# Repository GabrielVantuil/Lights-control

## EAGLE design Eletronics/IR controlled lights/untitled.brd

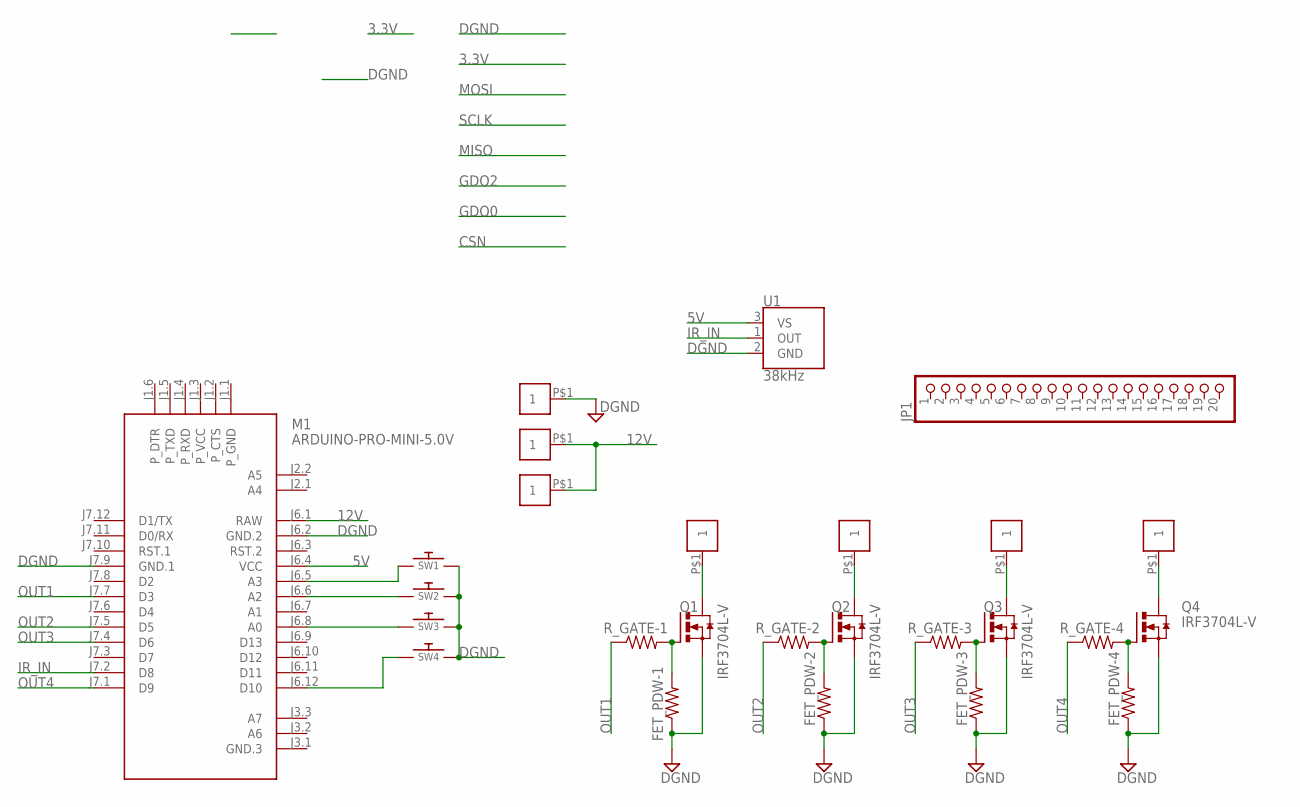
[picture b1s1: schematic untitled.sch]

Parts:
FET_PDW-1, FET_PDW-2, FET_PDW-3, FET_PDW-4: RESISTOR0603-RES; 0603-RES
JP1: PINHD-1X20; 1X20
M1: ARDUINO-PRO-MINI-5.0V; ARDUINO-PRO-MINI
Q1, Q2, Q3, Q4: IRF3704L-V; TO262-V
R_GATE-1, R_GATE-2, R_GATE-3, R_GATE-4: RESISTOR0603-RES; 0603-RES
SW1, SW2, SW3, SW4: SWITCH_PUSHBUTTONC&K_KSS; BTN_CK_KSS
U1: 38kHz; TSOP382
U$2, U$3, U$4, U$5, U$6, U$7, U$8: 1X01_2.54MM

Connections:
5V: M1.J6.4 (VCC), U1.3 (VS)
12V: M1.J6.1 (RAW), U$5.P$1, U$8.P$1
DGND: FET_PDW-1.1, FET_PDW-2.1, FET_PDW-3.1, FET_PDW-4.1, M1.J6.2 (GND.2), M1.J7.9 (GND.1), Q1.3 (S), Q2.3 (S), Q3.3 (S), Q4.3 (S), SW1.P$2, SW2.P$2, SW3.P$2, SW4.P$2, U1.2 (GND), U$7.P$1
IR_IN: M1.J7.2 (D8), U1.1 (OUT)
unnamed: FET_PDW-1.2, Q1.1 (G), R_GATE-1.2
unnamed: FET_PDW-2.2, Q2.1 (G), R_GATE-2.2
unnamed: FET_PDW-3.2, Q3.1 (G), R_GATE-3.2
unnamed: Q1.2 (D), U$2.P$1
unnamed: Q2.2 (D), U$3.P$1
unnamed: Q3.2 (D), U$4.P$1
unnamed: FET_PDW-4.2, Q4.1 (G), R_GATE-4.2
unnamed: Q4.2 (D), U$6.P$1
unnamed: M1.J6.5 (A3), SW1.P$1
unnamed: M1.J6.6 (A2), SW2.P$1
unnamed: M1.J6.8 (A0), SW3.P$1
unnamed: M1.J6.12 (D10), SW4.P$1
OUT1: M1.J7.7 (D3), R_GATE-1.1
OUT2: M1.J7.5 (D5), R_GATE-2.1
OUT3: M1.J7.4 (D6), R_GATE-3.1
OUT4: M1.J7.1 (D9), R_GATE-4.1

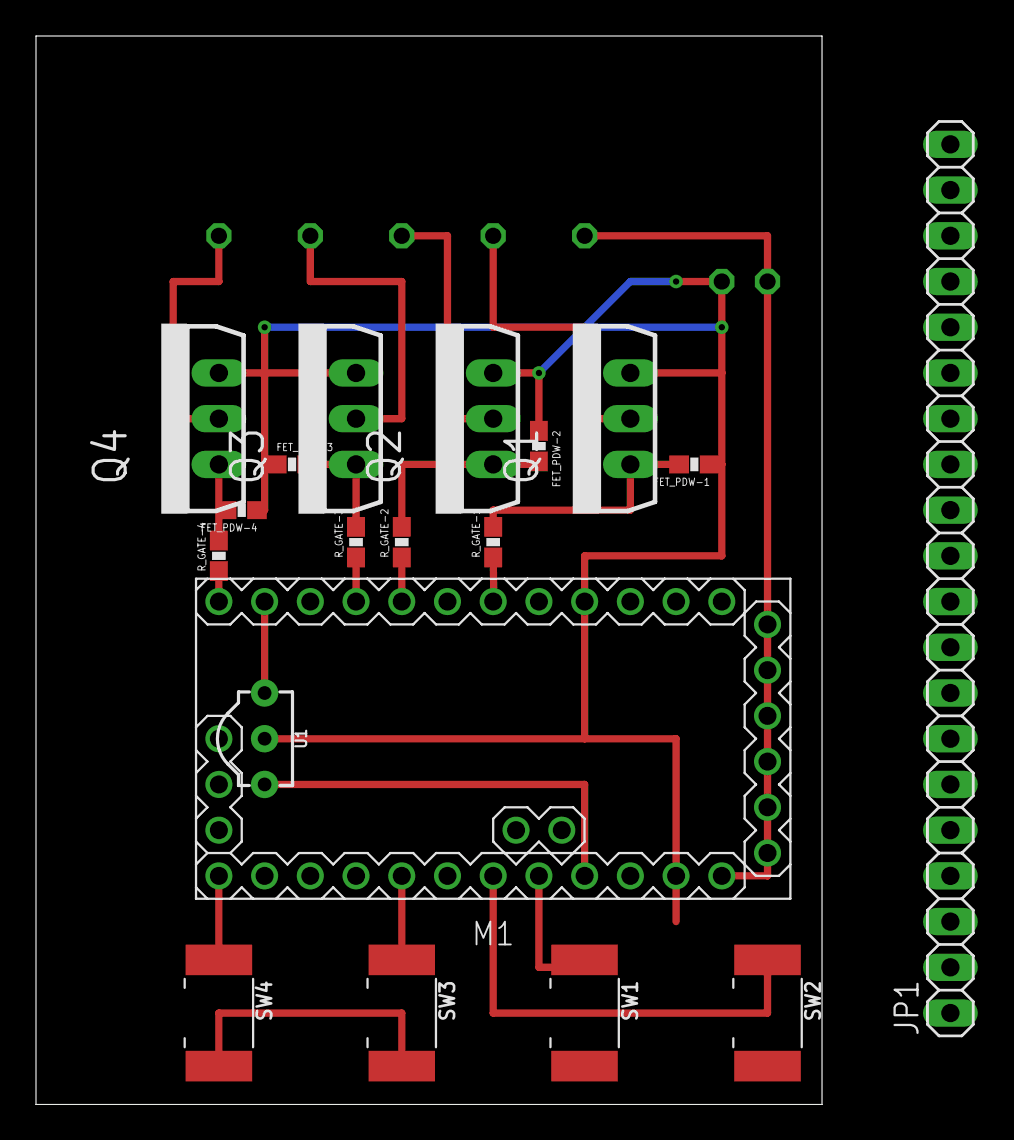
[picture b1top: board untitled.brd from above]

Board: 2 copper layers, 43.7 x 59.4 mm, 26 parts (0 on the bottom side), 20 nets.

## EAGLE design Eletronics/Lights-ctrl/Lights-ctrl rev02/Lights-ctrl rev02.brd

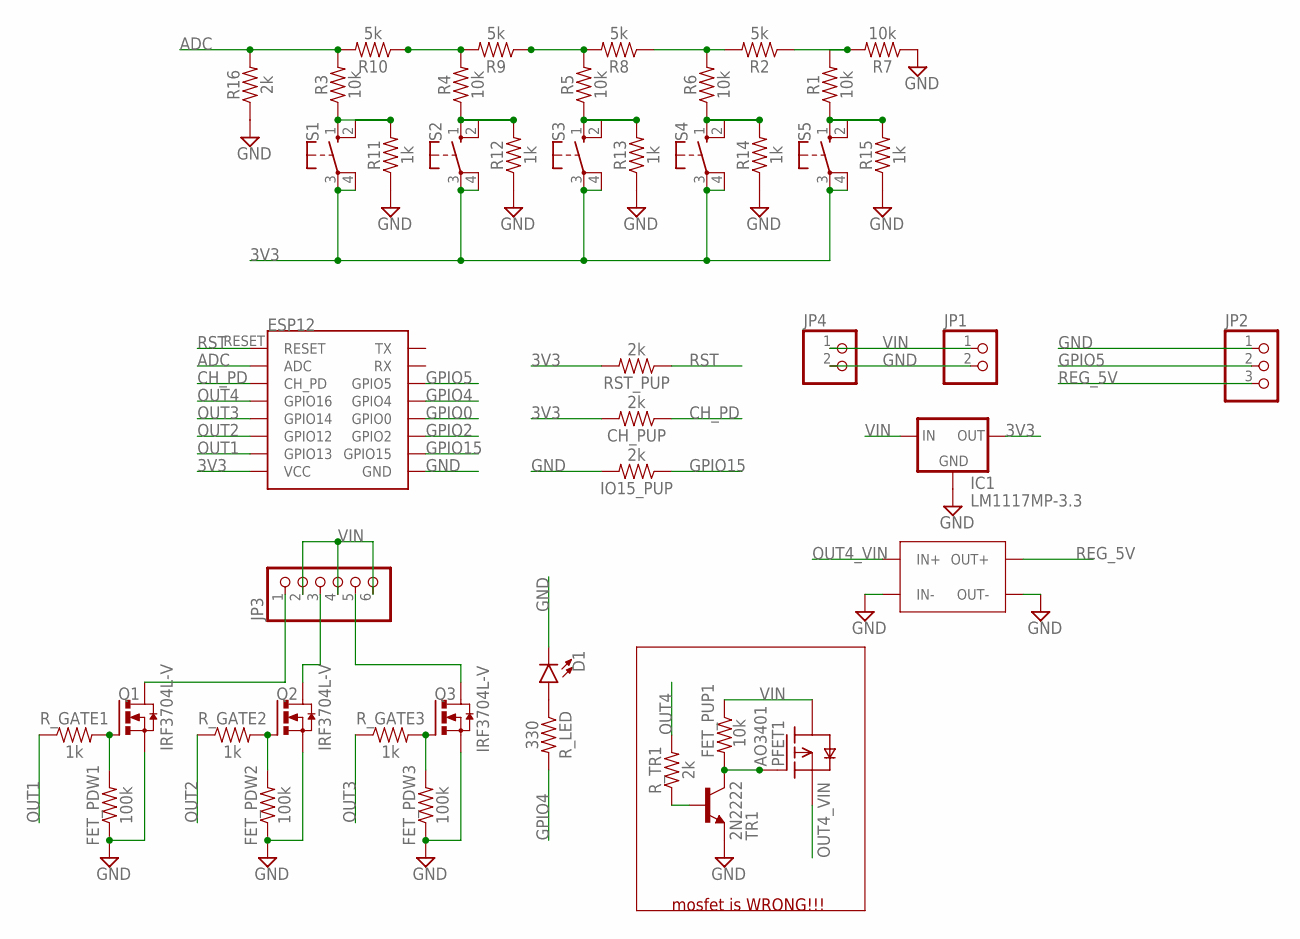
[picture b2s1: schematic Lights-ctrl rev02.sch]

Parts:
CH_PUP: 2k; 0603
D1: LED5MM-KIT; LED_5MM-KIT
FET_PDW1, FET_PDW2, FET_PDW3: 100k; 0603
FET_PUP1: 10k; 0603
IC1: LM1117MP-3.3; SOT223
IO15_PUP: 2k; 0603
JP1, JP4: PINHD-1X2; 1X02
JP2: PINHD-1X3; 1X03
JP3: PINHD-1X6/90; 1X06/90
PFET1: AO3401; SOT23-3
Q1, Q2, Q3: IRF3704L-V; TO262-V
R1, R3, R4, R5, R6, R7: 10k; 0603
R2, R8, R9, R10: 5k; 0603
R11, R12, R13, R14, R15: 1k; 0603
R16: 2k; 0603
RST_PUP: 2k; 0603
R_GATE1, R_GATE2, R_GATE3: 1k; 0603
R_LED: 330; 0603
R_TR1: 2k; 0603
S1, S2, S3, S4, S5: 10-XX; B3F-10XX
TR1: 2N2222; SOT23-BEC
U$1: ESP12E-CASTELLATED
U$4: XL4005

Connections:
3V3: CH_PUP.2, IC1.2 (OUT), IC1.4 (OUT), RST_PUP.2, S1.3, S1.4 (P1), S2.3, S2.4 (P1), S3.3, S3.4 (P1), S4.3, S4.4 (P1), S5.3, S5.4 (P1), U$1.VCC
ADC: R3.2, R10.2, R16.2, U$1.ADC
CH_PD: CH_PUP.1, U$1.CH_PD
GND: D1.K (C), FET_PDW1.1, FET_PDW2.1, FET_PDW3.1, IC1.1 (GND), IO15_PUP.2, JP1.2, JP2.1, JP4.2, Q1.3 (S), Q2.3 (S), Q3.3 (S), R7.1, R11.1, R12.1, R13.1, R14.1, R15.1, R16.1, TR1.E, U$1.GND, U$4.IN-, U$4.OUT-
GPIO0: U$1.GPIO0
GPIO2: U$1.GPIO2
GPIO4: R_LED.2, U$1.GPIO4
GPIO5: JP2.2, U$1.GPIO5
GPIO15: IO15_PUP.1, U$1.GPIO15
unnamed: JP3.1, Q1.2 (D)
unnamed: R2.2, R6.2, R8.1
unnamed: R5.2, R8.2, R9.1
unnamed: R4.2, R9.2, R10.1
unnamed: D1.A, R_LED.1
unnamed: R3.1, R11.2, S1.1 (S), S1.2 (S1)
unnamed: R_TR1.1, TR1.B
unnamed: FET_PUP1.2, PFET1.1 (G), TR1.C
unnamed: R1.1, R15.2, S5.1 (S), S5.2 (S1)
unnamed: JP3.3, Q2.2 (D)
unnamed: JP3.5, Q3.2 (D)
unnamed: FET_PDW1.2, Q1.1 (G), R_GATE1.2
unnamed: R1.2, R2.1, R7.2
unnamed: R4.1, R12.2, S2.1 (S), S2.2 (S1)
unnamed: FET_PDW2.2, Q2.1 (G), R_GATE2.2
unnamed: FET_PDW3.2, Q3.1 (G), R_GATE3.2
unnamed: R5.1, R13.2, S3.1 (S), S3.2 (S1)
unnamed: R6.1, R14.2, S4.1 (S), S4.2 (S1)
OUT1: R_GATE1.1, U$1.GPIO13
OUT2: R_GATE2.1, U$1.GPIO12
OUT3: R_GATE3.1, U$1.GPIO14
OUT4: R_TR1.2, U$1.GPIO16
OUT4_VIN: PFET1.2 (S), U$4.IN+
REG_5V: JP2.3, U$4.OUT+
RST: RST_PUP.1, U$1.RESET
VIN: FET_PUP1.1, IC1.3 (IN), JP1.1, JP3.2, JP3.4, JP3.6, JP4.1, PFET1.3 (D)

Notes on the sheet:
mosfet is WRONG!!!

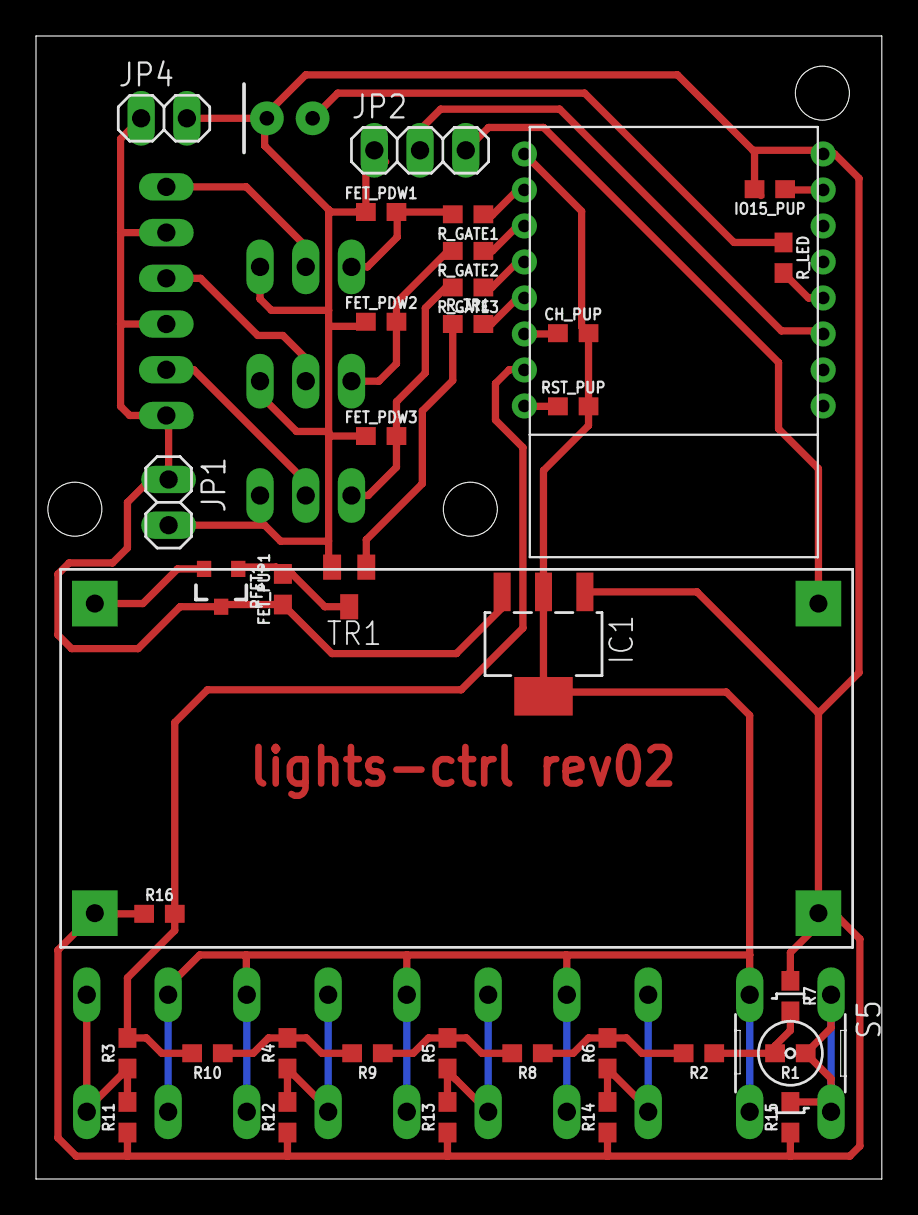
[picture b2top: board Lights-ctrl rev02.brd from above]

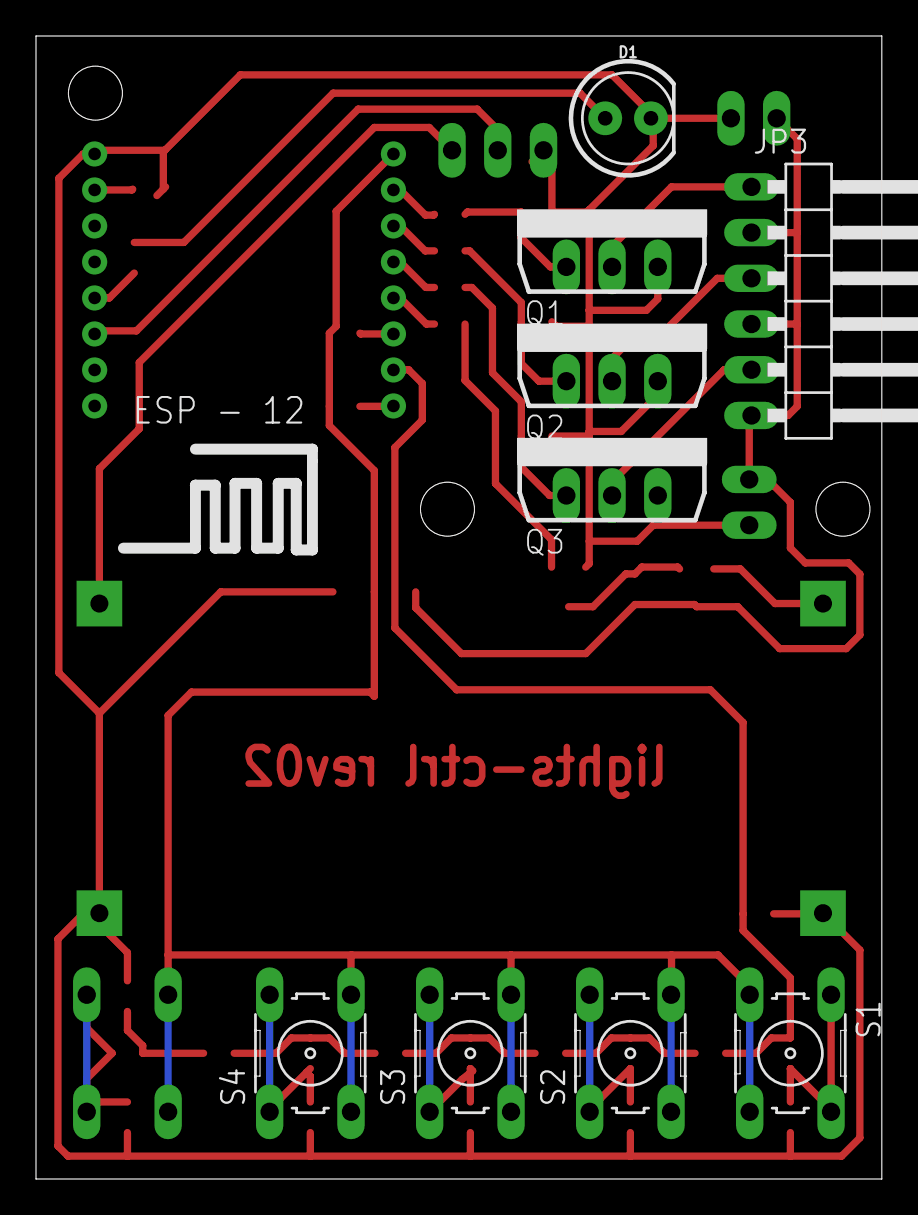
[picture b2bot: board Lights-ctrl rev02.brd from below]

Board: 2 copper layers, 47.0 x 63.5 mm, 46 parts (10 on the bottom side), 33 nets.

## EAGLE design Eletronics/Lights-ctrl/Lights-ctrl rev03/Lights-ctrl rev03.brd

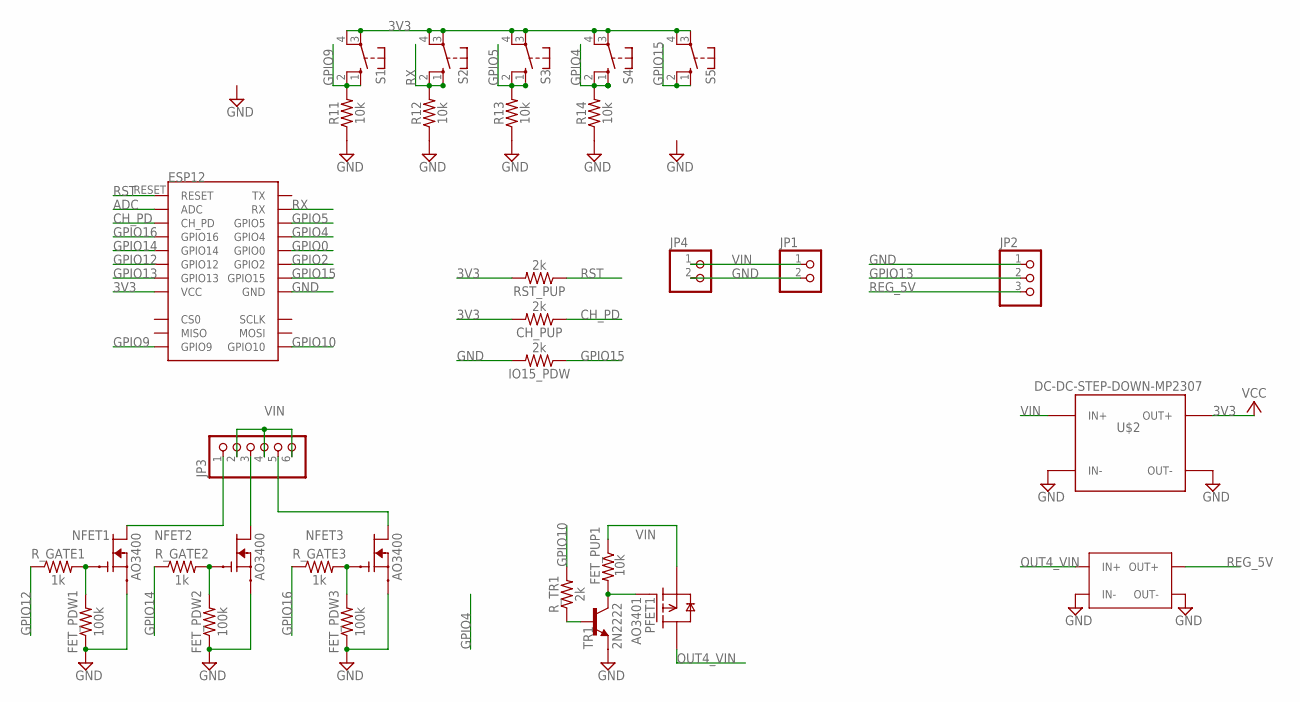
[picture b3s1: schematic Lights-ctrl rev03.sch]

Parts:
CH_PUP: 2k; 0603
FET_PDW1, FET_PDW2, FET_PDW3: 100k; 0603
FET_PUP1: 10k; 0603
IO15_PDW: 2k; 0603
JP1, JP4: PINHD-1X2; 1X02
JP2: PINHD-1X3; 1X03
JP3: PINHD-1X6/90; 1X06/90
NFET1, NFET2, NFET3: AO3400; SOT23-3
PFET1: AO3401; SOT23-3
R11, R12, R13, R14: 10k; 0603
RST_PUP: 2k; 0603
R_GATE1, R_GATE2, R_GATE3: 1k; 0603
R_TR1: 2k; 0603
S1, S2, S3, S4, S5: 10-XX; B3F-10XX
TR1: 2N2222; SOT23-BEC
U$1: ESP12E-CASTELLATED
U$2: DC-DC-STEP-DOWN-MP2307
U$4: XL4005

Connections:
3V3: CH_PUP.2, RST_PUP.2, S1.3, S1.4 (P1), S2.3, S2.4 (P1), S3.3, S3.4 (P1), S4.3, S4.4 (P1), S5.3, S5.4 (P1), U$1.VCC, U$2.OUT+
ADC: U$1.ADC
CH_PD: CH_PUP.1, U$1.CH_PD
GND: FET_PDW1.1, FET_PDW2.1, FET_PDW3.1, IO15_PDW.2, JP1.2, JP2.1, JP4.2, NFET1.2 (S), NFET2.2 (S), NFET3.2 (S), R11.1, R12.1, R13.1, R14.1, TR1.E, U$1.GND, U$2.IN-, U$2.OUT-, U$4.IN-, U$4.OUT-
GPIO0: U$1.GPIO0
GPIO2: U$1.GPIO2
GPIO4: R14.2, S4.1 (S), S4.2 (S1), U$1.GPIO4
GPIO5: R13.2, S3.1 (S), S3.2 (S1), U$1.GPIO5
GPIO9: R11.2, S1.1 (S), S1.2 (S1), U$1.GPIO9
GPIO10: R_TR1.2, U$1.GPIO10
GPIO12: R_GATE1.1, U$1.GPIO12
GPIO13: JP2.2, U$1.GPIO13
GPIO14: R_GATE2.1, U$1.GPIO14
GPIO15: IO15_PDW.1, S5.1 (S), S5.2 (S1), U$1.GPIO15
GPIO16: R_GATE3.1, U$1.GPIO16
unnamed: JP3.1, NFET1.3 (D)
unnamed: R_TR1.1, TR1.B
unnamed: FET_PUP1.2, PFET1.1 (G), TR1.C
unnamed: JP3.3, NFET2.3 (D)
unnamed: JP3.5, NFET3.3 (D)
unnamed: FET_PDW1.2, NFET1.1 (G), R_GATE1.2
unnamed: FET_PDW2.2, NFET2.1 (G), R_GATE2.2
unnamed: FET_PDW3.2, NFET3.1 (G), R_GATE3.2
OUT4_VIN: PFET1.3 (D), U$4.IN+
REG_5V: JP2.3, U$4.OUT+
RST: RST_PUP.1, U$1.RESET
RX: R12.2, S2.1 (S), S2.2 (S1), U$1.RX
VIN: FET_PUP1.1, JP1.1, JP3.2, JP3.4, JP3.6, JP4.1, PFET1.2 (S), U$2.IN+

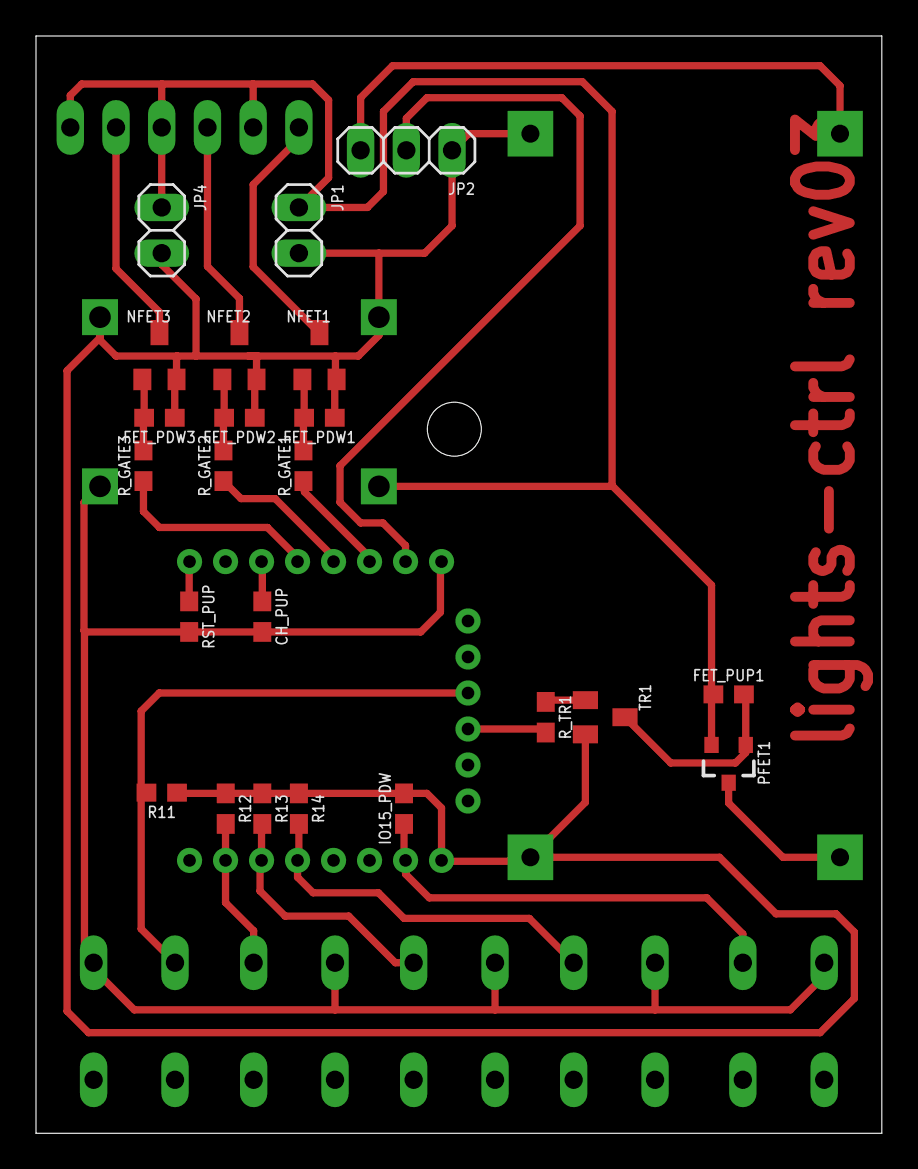
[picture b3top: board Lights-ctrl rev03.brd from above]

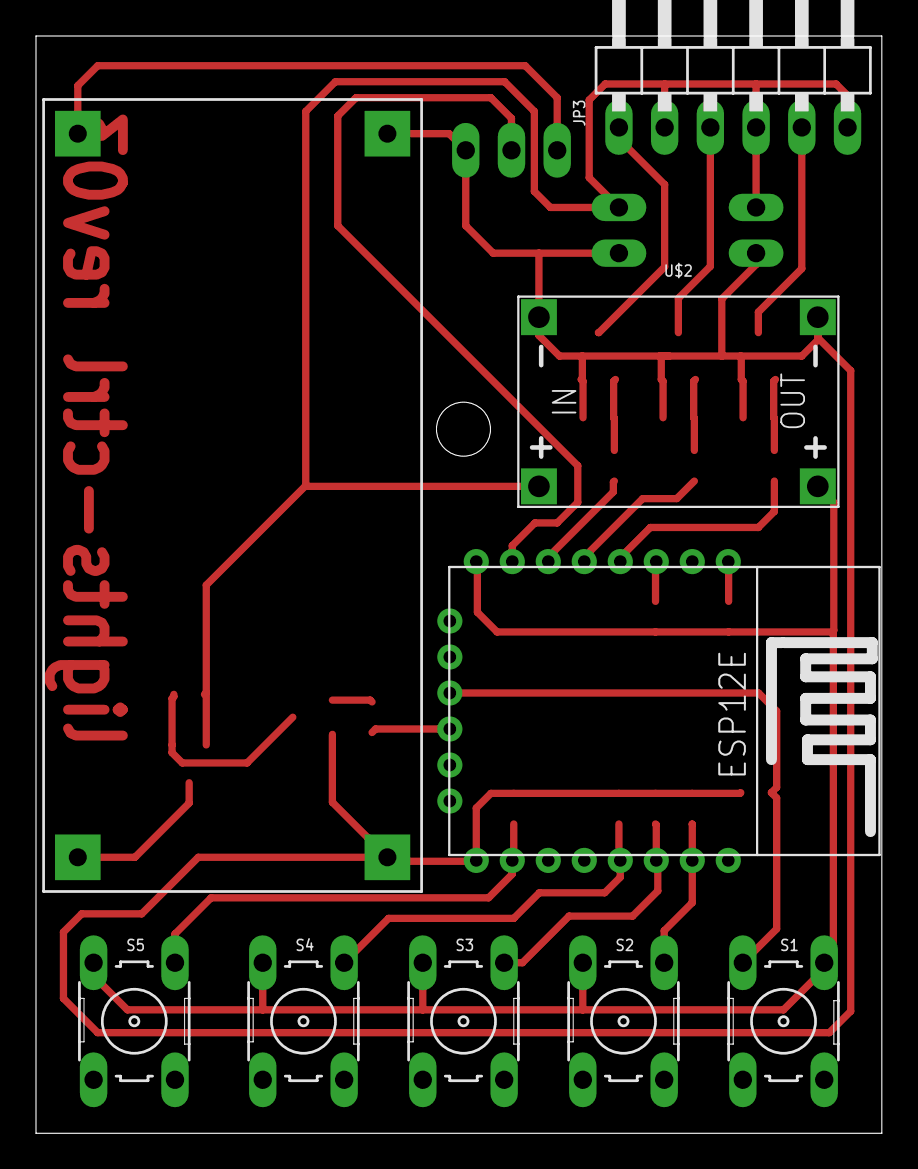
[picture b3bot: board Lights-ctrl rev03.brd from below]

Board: 2 copper layers, 47.0 x 61.0 mm, 32 parts (9 on the bottom side), 25 nets.

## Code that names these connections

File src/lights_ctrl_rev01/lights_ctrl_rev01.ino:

#include <ESP8266WiFi.h>
#include <WiFiClient.h>
#include <ESP8266WebServer.h>
#include <ESP8266mDNS.h>
#include <ESP8266HTTPUpdateServer.h>

#ifndef STASSID
#define STASSID ""
#define STAPSK  ""
#endif

const char* host = "lights";
const char* ssid = STASSID;
const char* password = STAPSK;


#define OUT1 13
#define OUT2 12
#define OUT3 14
#define OUT4 16
#define IR_LED 4
#define NEOPIXEL 5

int numPixels   = 120;


//------------------ neopixel--------------------
#include <Adafruit_NeoPixel.h>
#ifdef __AVR__
#include <avr/power.h> // Required for 16 MHz Adafruit Trinket
#endif

const int neopixel_pin =  NEOPIXEL;
int pixelFormat = NEO_GRBW + NEO_KHZ800;

Adafruit_NeoPixel *pixels;

//------------------ HTTP--------------------

ESP8266WebServer server(80);
ESP8266HTTPUpdateServer httpUpdater;

const int led = 2;
String filaLeds;

void setup(void) {
  #if defined(__AVR_ATtiny85__) && (F_CPU == 16000000)
    clock_prescale_set(clock_div_1);
  #endif

  pixels = new Adafruit_NeoPixel(numPixels, neopixel_pin, pixelFormat);
  pixels->begin(); // INITIALIZE NeoPixel strip object (REQUIRED)

  pixels->setPixelColor(10, pixels->Color(255,255,255,255));
  delay(1000);
  pixels->clear(); // Set all pixel colors to 'off'

  pinMode(OUT1, OUTPUT);
  pinMode(OUT2, OUTPUT);
  pinMode(OUT3, OUTPUT);
  pinMode(OUT4, OUTPUT);
  pinMode(2, OUTPUT);
  analogWrite(2, 0);
  
  Serial.begin(115200);
  WiFi.mode(WIFI_STA);
  WiFi.begin(ssid, password);
  Serial.println("");

  // Wait for connection
  while (WiFi.status() != WL_CONNECTED) {
    delay(500);
    Serial.print(".");
  }

  Serial.println("");
  Serial.print("Connected to ");
  Serial.println(ssid);
  Serial.print("IP address: ");
  Serial.println(WiFi.localIP());
//
//  if (MDNS.begin("esp8266")) {
//    Serial.println("MDNS responder started");
//  }
  

  //MDNS.begin(host);

  httpUpdater.setup(&server);

  //MDNS.addService("http", "tcp", 80);
  Serial.printf("HTTPUpdateServer ready! Open http://%s.local/update in your browser\n", host);
  Serial.print("IP address: ");
  Serial.println(WiFi.localIP());
  

  //server.on("/", handleRoot);
  server.on("/OUT1", d_Out1);
  server.on("/OUT2", d_Out2);
  server.on("/OUT3", d_Out3);
  server.on("/OUT4", d_Out4);
  server.on("/clear", []() {
    pixels->clear();
    server.send(200, "text/plain", "this works as well");
  });
  server.on("/digitalOut", digitalOut);
  server.on("/setpixel", neopixel_setpixel);
  server.on("/setpixelRange", neopixel_setpixelRange);
  server.on("/pixelAnimacao", neopixel_pixelAnimacao);
  server.on("/ping", ping);
  server.on("/help", help);
  server.onNotFound(handleNotFound);
  server.begin();
  Serial.println("HTTP server started");
  analogWrite(2, 254);  
}
int delayNext, startLed, endLed, filaR, filaG, filaB, filaW, nextLed;
void loop(void) {
  server.handleClient();
  //MDNS.update();

  if (filaLeds.length() != 0) {
    if (nextLed == endLed) {
      if (filaLeds == "FIM") {
        filaLeds.remove(0);
      }
      else {
        delayNext = filaLeds.substring(0, filaLeds.indexOf('.') + 1).toInt();
        filaLeds.remove(0, filaLeds.indexOf('.') + 1);
        filaR = filaLeds.substring(0, filaLeds.indexOf(',') + 1).toInt();
        filaLeds.remove(0, filaLeds.indexOf(',') + 1);
        filaG = filaLeds.substring(0, filaLeds.indexOf(',') + 1).toInt();
        filaLeds.remove(0, filaLeds.indexOf(',') + 1);
        filaB = filaLeds.substring(0, filaLeds.indexOf(',') + 1).toInt();
        filaLeds.remove(0, filaLeds.indexOf(',') + 1);
        filaW = filaLeds.substring(0, filaLeds.indexOf(',') + 1).toInt();
        filaLeds.remove(0, filaLeds.indexOf(',') + 1);
        startLed = filaLeds.substring(0, filaLeds.indexOf(',') + 1).toInt();
        filaLeds.remove(0, filaLeds.indexOf(',') + 1);
        endLed = filaLeds.substring(0, filaLeds.indexOf(',') + 1).toInt();
        filaLeds.remove(0, filaLeds.indexOf(',') + 1);
        nextLed = startLed;
      }
    }
    else{
      nextLed += abs(endLed - startLed) / (endLed - startLed);
    }
    pixels->setPixelColor(nextLed, pixels->Color(filaR, filaG, filaB, filaW));
    long start = millis();
    while (millis() < start + delayNext);
    pixels->show();
  }


}

void digitalOut() {
  String arguments = "Comando(s) aceito(s): \n";
  for (uint8_t i = 0; i < server.args(); i++) {
    if (server.argName(i) == "change") {
      digitalWrite(server.arg(i).toInt(), !digitalRead(server.arg(i).toInt()));
      arguments += String(i) + ") Status da porta " + server.arg(i).toInt() + " alterado para: " + ((digitalRead(server.arg(i).toInt()) == 0) ? "LOW" : "HIGH") + "\n";
    }
    else {
      arguments += String(i) + ") Enviando para porta " + server.argName(i) + ": " + ((server.arg(i).toInt() == 0) ? "LOW" : "HIGH") + "\n";
      digitalWrite(server.argName(i).toInt(), server.arg(i).toInt() == 0 ? LOW : HIGH);
    }
  }
  Serial.println(arguments);

  server.send(404, "text/plain", arguments);
}

void d_Out1(){digitalWrite(OUT1, !digitalRead(OUT1)); server.send(200, "text/plain", "Command accepted");}
void d_Out2(){digitalWrite(OUT2, !digitalRead(OUT2)); server.send(200, "text/plain", "Command accepted");}
void d_Out3(){digitalWrite(OUT3, !digitalRead(OUT3)); server.send(200, "text/plain", "Command accepted");}
void d_Out4(){digitalWrite(OUT4, !digitalRead(OUT4)); server.send(200, "text/plain", "Command accepted");}

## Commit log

2025-01-17 Commiting old code
2025-01-17 git-ignore
2025-01-18 Some refactoring (still a lot to be done), started adding alexa, but it looks like it isnt working with another http server

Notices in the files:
parts and their libraries:
diy modules: Released under the Creative Commons Attribution 4.0 International License: http://creativecommons.org/licenses/by/4.0
sparkFun-Sensors: Licensing: Creative Commons ShareAlike 4.0 International - https://creativecommons.org/licenses/by-sa/4.0
